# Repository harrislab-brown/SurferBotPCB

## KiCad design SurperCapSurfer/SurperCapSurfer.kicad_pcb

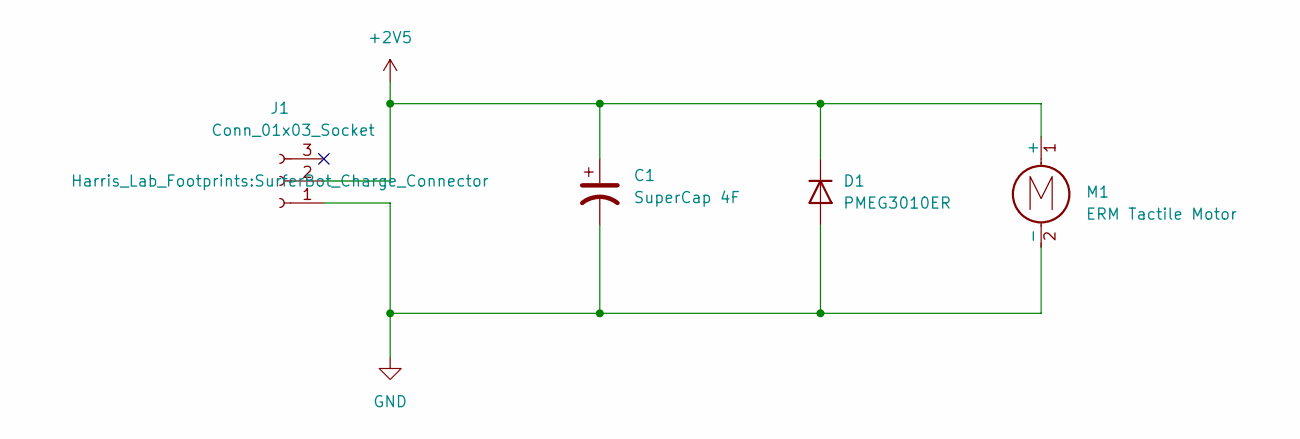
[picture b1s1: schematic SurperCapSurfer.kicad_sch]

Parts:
C1: SuperCap 4F; CP_Radial_D6.3mm_P2.50mm
D1: PMEG3010ER; D_SOD-123
J1: Conn_01x03_Socket; SurferBot_Charge_Connector
M1: ERM Tactile Motor; ERM_Motor_Pads

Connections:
+2V5: C1.1, D1.1 (K), J1.2, M1.1 (+)
GND: C1.2, D1.2 (A), J1.1, M1.2 (-)

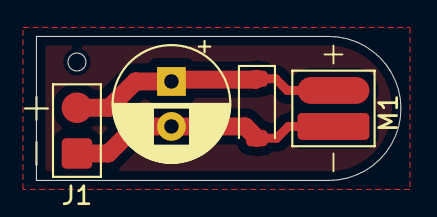
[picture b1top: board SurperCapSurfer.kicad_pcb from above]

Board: 2 copper layers, 20.2 x 8.0 mm, 4 parts (0 on the bottom side), 2 nets.

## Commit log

2025-05-18 V2 of PCB milled
2025-05-20 final board design, about to try panelization
2025-05-20 created cnc files, cut out V2 pcbs
2025-05-20 example edit
2025-05-20 added folder for MCAD
